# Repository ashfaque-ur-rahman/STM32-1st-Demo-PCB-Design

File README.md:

# STM32 Demo PCB Design
 
My first STM32 microcontroller PCB design, built following the **Phil's Lab STM32 PCB Design tutorial series**. This project was a foundational learning experience in professional PCB design workflow — from schematic capture to layout, design rule checking, and Gerber file generation for manufacturing.
 
---
 
## Preview
 
### Schematic

### PCB Layout

### 3D View

---
 
## Project overview
 
| Property | Details |
|---|---|
| **MCU** | STM32 |
| **EDA Tool** | KiCad |
| **Board layers** | 2-layer |
| **Design reference** | Phil's Lab — STM32 PCB Design Series |
| **Status** | Design complete — Gerbers exported |
 
---
 
## Files included
 
### KiCad project files
| File | Description |
|---|---|
| `STM32_1st_Project.kicad_pro` | KiCad project file |
| `STM32_1st_Project.kicad_sch` | Schematic |
| `STM32_1st_Project.kicad_pcb` | PCB layout |
| `STM32_1st_Project.kicad_prl` | Local settings |
 
### Gerber files (manufacturing-ready)
| File | Layer |
|---|---|
| `STM32_1st_Project-F_Cu.gbr` | Front copper layer |
| `STM32_1st_Project-B_Cu.gbr` | Back copper layer |
| `STM32_1st_Project-F_Mask.gbr` | Front solder mask |
| `STM32_1st_Project-B_Mask.gbr` | Back solder mask |
| `STM32_1st_Project-F_Paste.gbr` | Front solder paste |
| `STM32_1st_Project-B_Paste.gbr` | Back solder paste |
| `STM32_1st_Project-F_Silkscreen.gbr` | Front silkscreen |
| `STM32_1st_Project-B_Silkscreen.gbr` | Back silkscreen |
| `STM32_1st_Project-Edge_Cuts.gbr` | Board outline |
| `STM32_1st_Project-PTH.drl` | Plated through-holes drill file |
| `STM32_1st_Project-NPTH.drl` | Non-plated through-holes drill file |
 
### Assembly files
| File | Description |
|---|---|
| `STM32_1st_Project-top-pos.csv` | Top component placement positions |
| `STM32_1st_Project-bottom-pos.csv` | Bottom component placement positions |
 
---
 
## What I learned
 
- STM32 microcontroller schematic design and symbol placement
- Decoupling capacitor placement for power supply stability
- 2-layer PCB stackup and copper pour design
- Design Rule Check (DRC) and error resolution
- Gerber file generation and validation for PCB manufacturing
- KiCad project workflow from schematic to production files
---
 
## Tools used

---
 
## Reference
 
This design follows the **Phil's Lab STM32 PCB Design tutorial series** — an excellent resource for learning professional PCB design practices with KiCad.
 
> Phil's Lab: [https://www.youtube.com/@PhilsLab](https://www.youtube.com/@PhilsLab)
 
---
 
*Mymensingh Engineering College — EEE Department*

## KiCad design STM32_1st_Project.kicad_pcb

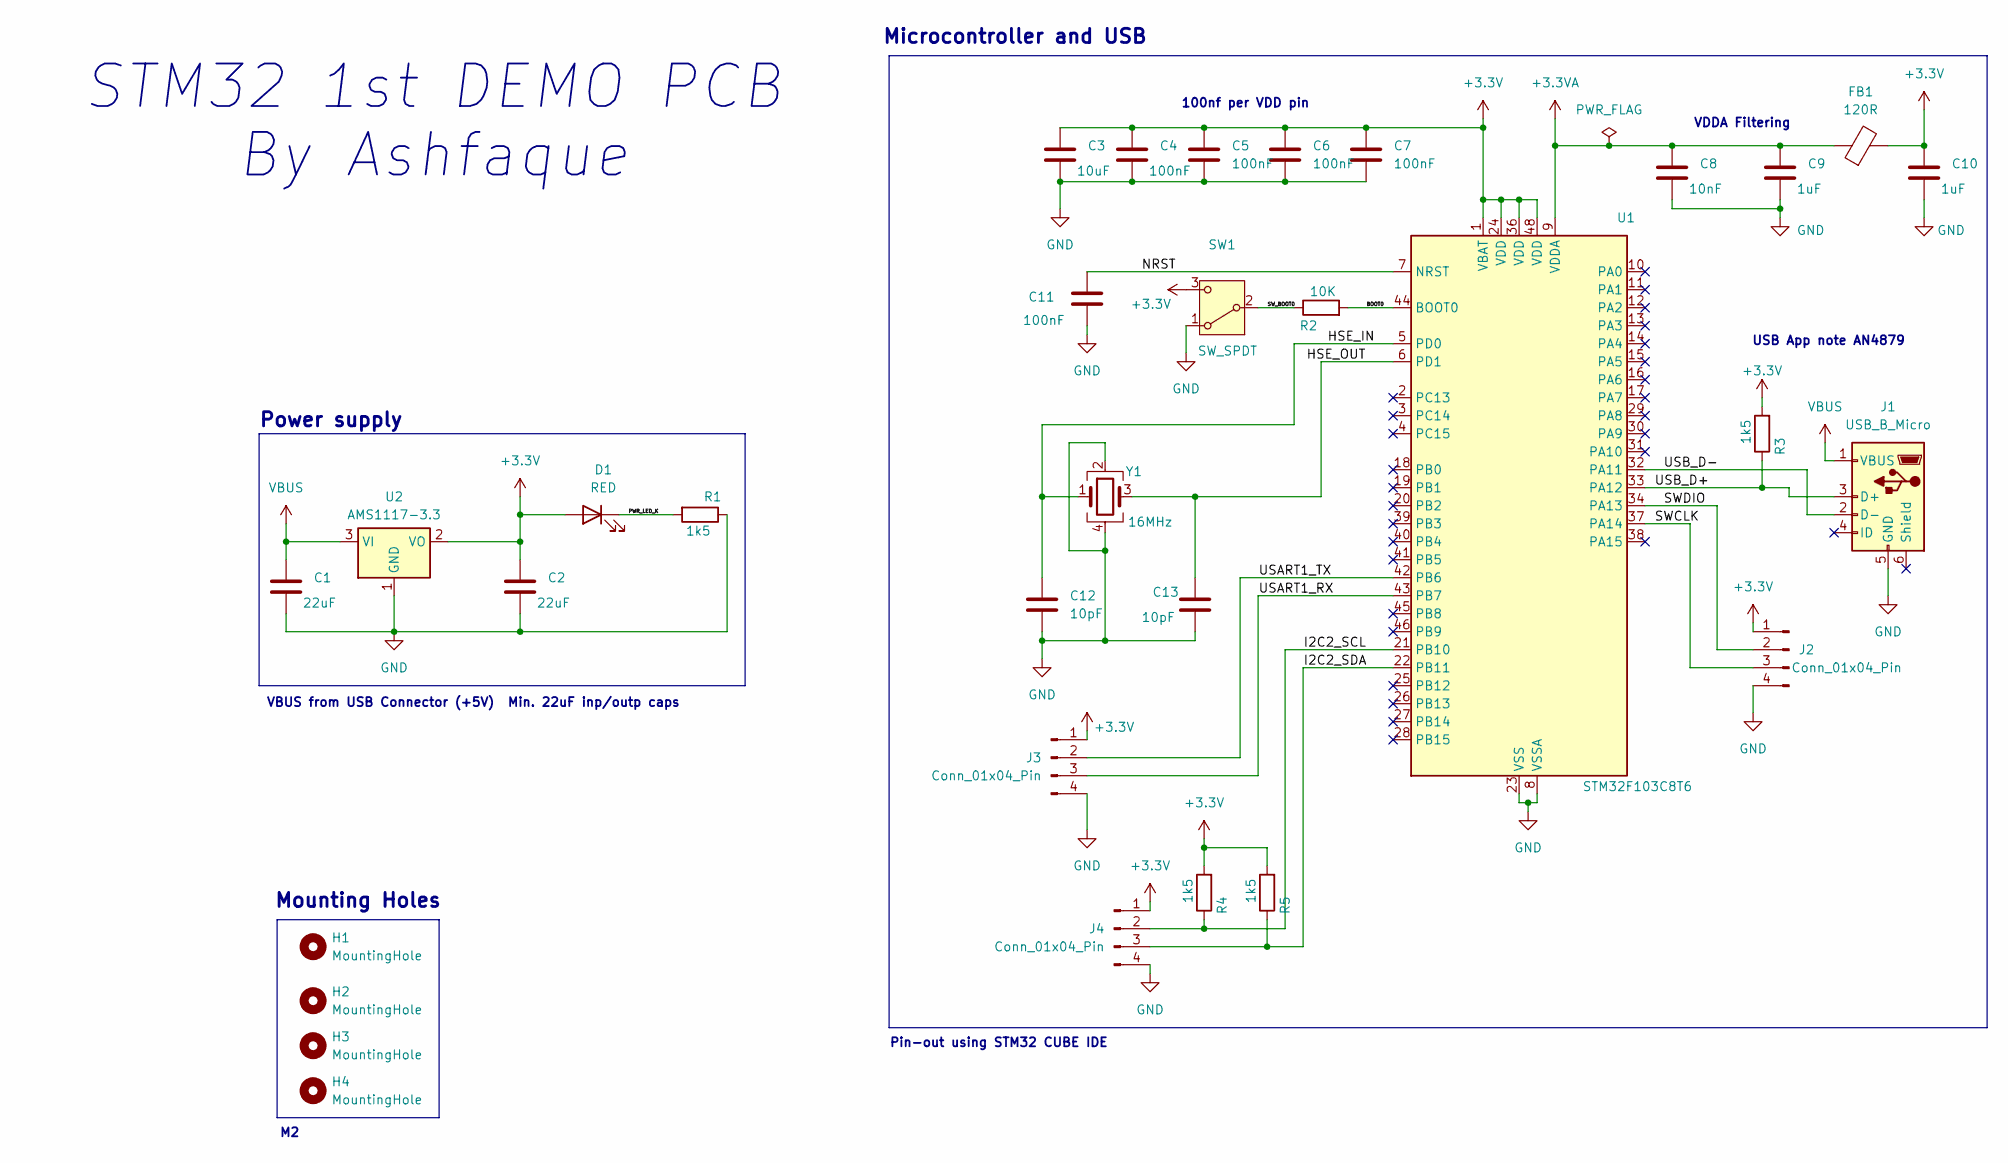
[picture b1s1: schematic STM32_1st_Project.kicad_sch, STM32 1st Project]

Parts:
C1, C2: 22uF; C_0805_2012Metric
C3: 10uF; C_0603_1608Metric
C4, C5, C6, C7, C11: 100nF; C_0402_1005Metric
C8: 10nF; C_0402_1005Metric
C9, C10: 1uF; C_0402_1005Metric
C12, C13: 10pF; C_0402_1005Metric
D1: RED; LED_0603_1608Metric
FB1: 120R; L_0603_1608Metric
H1, H2, H3, H4: MountingHole; MountingHole_2.2mm_M2
J1: USB_B_Micro; USB_Micro-B_Wuerth_629105150521
J2, J3, J4: Conn_01x04_Pin; PinHeader_1x04_P2.54mm_Vertical
R1, R3, R4, R5: 1k5; R_0402_1005Metric
R2: 10K; R_0402_1005Metric
SW1: SW_SPDT; SW_SPDT_PCM12
U1: STM32F103C8T6; LQFP-48_7x7mm_P0.5mm
U2: AMS1117-3.3; SOT-223-3_TabPin2
Y1: 16MHz; Crystal_SMD_3225-4Pin_3.2x2.5mm

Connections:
+3.3V: C2.1, C3.1, C4.1, C5.1, C6.1, C7.1, C10.1, D1.2 (A), FB1.2, J2.1, J3.1, J4.1, R3.2, R4.2, R5.2, SW1.3 (C), U1.1 (VBAT), U1.24 (VDD), U1.36 (VDD), U1.48 (VDD), U2.2 (VO)
+3.3VA: C8.1, C9.1, FB1.1, U1.9 (VDDA)
/BOOT0: R2.2, U1.44 (BOOT0)
/HSE_IN: C12.1, U1.5 (PD0), Y1.1
/HSE_OUT: C13.1, U1.6 (PD1), Y1.3
/I2C2_SCL: J4.2, R4.1, U1.21 (PB10)
/I2C2_SDA: J4.3, R5.1, U1.22 (PB11)
/NRST: C11.1, U1.7 (NRST)
/PWR_LED_K: D1.1 (K), R1.2
/SWCLK: J2.3, U1.37 (PA14)
/SWDIO: J2.2, U1.34 (PA13)
/SW_BOOT0: R2.1, SW1.2 (B)
/USART1_RX: J3.3, U1.43 (PB7)
/USART1_TX: J3.2, U1.42 (PB6)
/USB_D+: J1.3 (D+), R3.1, U1.33 (PA12)
/USB_D-: J1.2 (D-), U1.32 (PA11)
GND: C1.2, C2.2, C3.2, C4.2, C5.2, C6.2, C7.2, C8.2, C9.2, C10.2, C11.2, C12.2, C13.2, J1.5 (GND), J2.4, J3.4, J4.4, R1.1, SW1.1 (A), U1.8 (VSSA), U1.23 (VSS), U1.35 (VSS), U1.47 (VSS), U2.1 (GND), Y1.2, Y1.4
VBUS: C1.1, J1.1 (VBUS), U2.3 (VI)

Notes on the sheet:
VBUS from USB Connector (+5V) Min. 22uF inp/outp caps
Power supply
Pin-out using STM32 CUBE IDE
USB App note AN4879
STM32 1st DEMO PCB By Ashfaque
100nf per VDD pin
Microcontroller and USB
Mounting Holes
VDDA Filtering

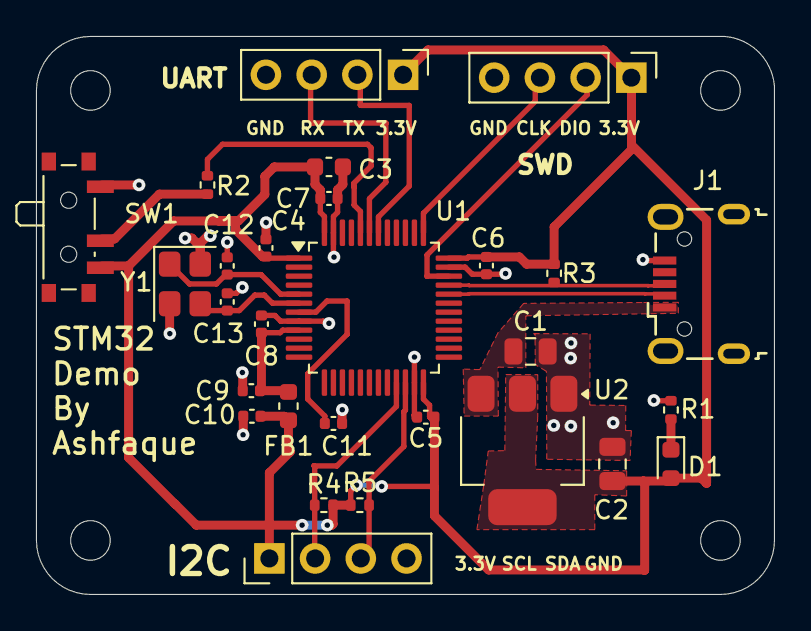
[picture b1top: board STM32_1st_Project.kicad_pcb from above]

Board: 2 copper layers, 41.0 x 31.0 mm, 32 parts (0 on the bottom side), 18 nets.
